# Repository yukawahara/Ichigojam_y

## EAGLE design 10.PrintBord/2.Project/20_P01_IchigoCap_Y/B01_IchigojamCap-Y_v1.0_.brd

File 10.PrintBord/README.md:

# フォルダ説明
* 0.Library
** パーツライブラリー、自作パーツ等を保存する

* 1.Tools
** Eagleで利用ツールを保存

* 2.Project
** Eagle でプロジェクトを作成した時に保存するもの
【プロジェクト命名規則】
プロジェクト名は下記とすること
```
年２桁_P連番_基盤名

例)
20_P01_EEPROM
```

【ボード命名規則】
プロジェクト名は下記とすること
```
B連番_基盤名_バージョン_備考

例)
B01_EEPROM_v1.0_〇〇
```

* 3.Order_Duplication
** 発注前に複製したデータを保存する。
** 保存する時は、「フォルダー」と「説明テキスト」を記載すること
【フォルダの命名規則】
```
年２桁_D連番_Pから始まるベースとなった基盤の番号-そのバージョン

例)
20_D01_P001-v1.0+P002-v1.0

```

* 10.Order
** 発注時に作成したデータを保存する。
** ここに保存するのは、ZIPファイルのみ
** 発注時に変更した時は

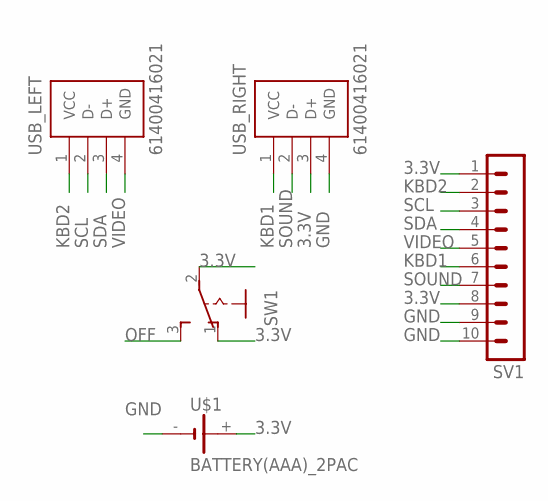
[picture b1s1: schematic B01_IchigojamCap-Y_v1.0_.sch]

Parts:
SV1: MA10-1
SW1: 255SB
U$1: BATTERY(AAA)_2PAC; BATTERY_HOLDER
USB_LEFT: 61400416021
USB_RIGHT: 61400416021

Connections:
3.3V: SV1.1, SV1.8, SW1.1 (O), SW1.2, U$1.+, USB_RIGHT.3 (D+)
GND: SV1.9, SV1.10, U$1.-, USB_RIGHT.4 (GND)
KBD1: SV1.6, USB_RIGHT.1 (VCC)
KBD2: SV1.2, USB_LEFT.1 (VCC)
OFF: SW1.3 (S)
SCL: SV1.3, USB_LEFT.2 (D-)
SDA: SV1.4, USB_LEFT.3 (D+)
SOUND: SV1.7, USB_RIGHT.2 (D-)
VIDEO: SV1.5, USB_LEFT.4 (GND)

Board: 2 copper layers, 5 parts (0 on the bottom side), 8 nets, no tracks yet.

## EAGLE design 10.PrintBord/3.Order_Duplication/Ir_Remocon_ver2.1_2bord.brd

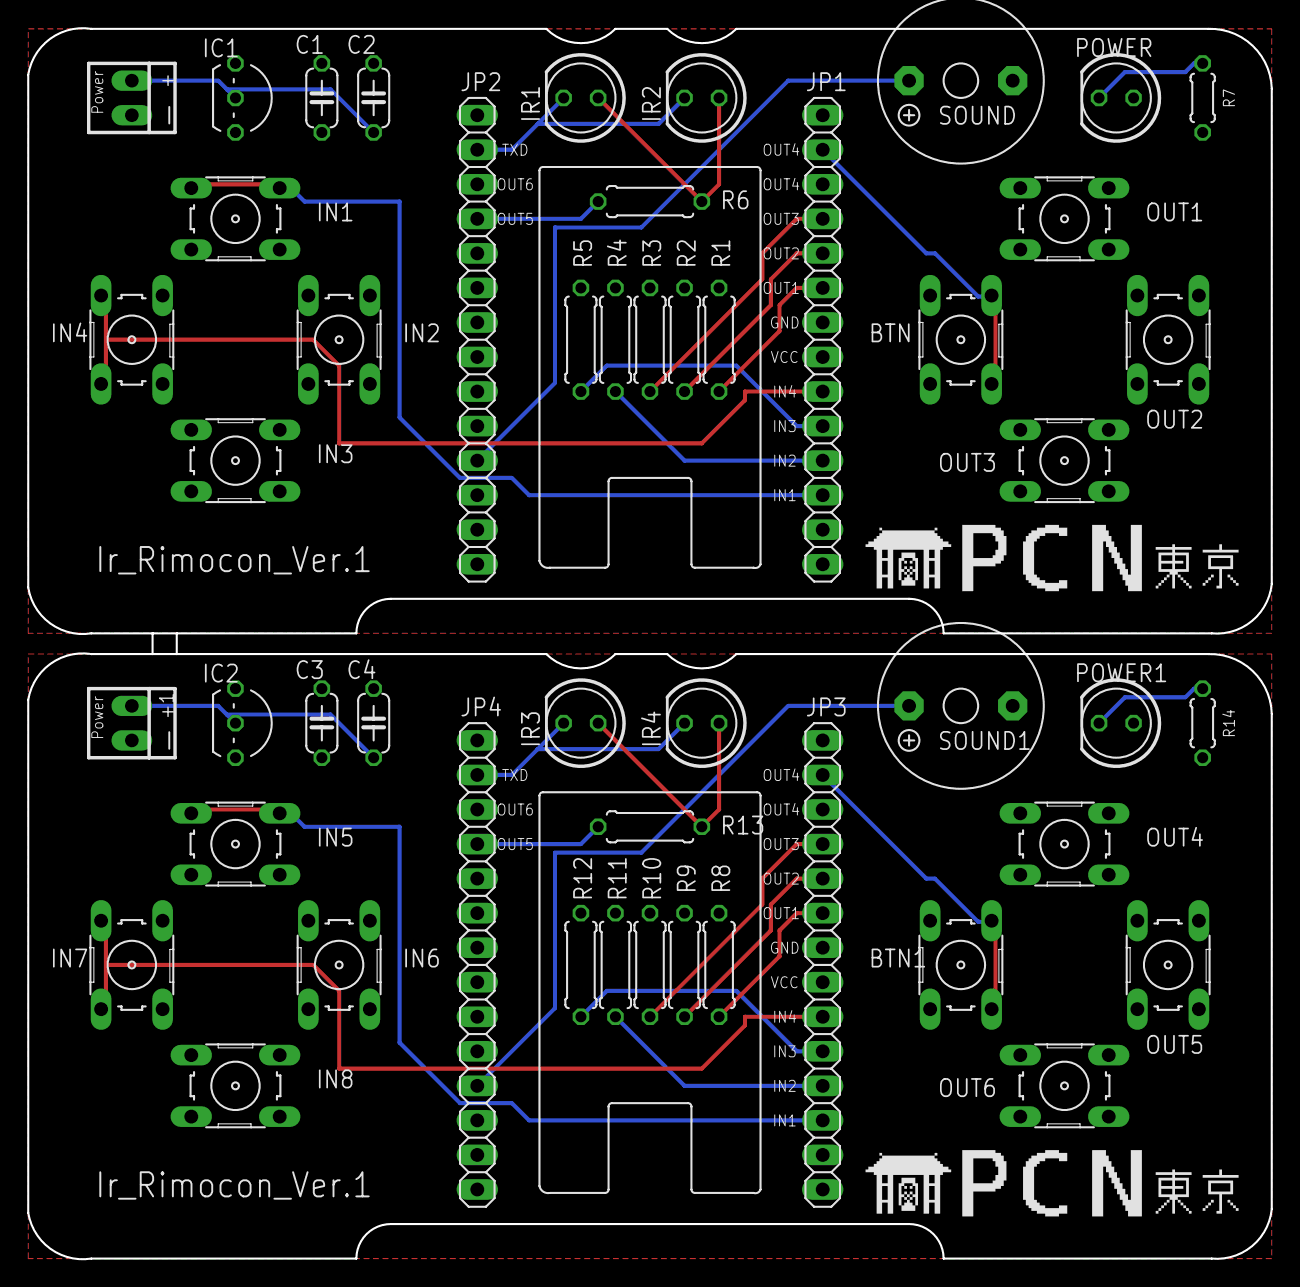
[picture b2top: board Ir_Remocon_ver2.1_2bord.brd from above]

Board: 2 copper layers, 91.4 x 90.5 mm, 50 parts (0 on the bottom side), 32 nets.

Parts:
+, +1: 22-23-2021
BTN, BTN1: B3F-10XX
C1, C2, C3, C4: C050-024X044
IC1, IC2: TO92-
IN1, IN2, IN3, IN4, IN5, IN6, IN7, IN8: B3F-10XX
IR1, IR2, IR3, IR4: LED5MM
JP1, JP2, JP3, JP4: 1X14
OUT1, OUT2, OUT3, OUT4, OUT5, OUT6: B3F-10XX
POWER, POWER1: LED5MM
R1, R2, R3, R4, R5, R8, R9, R10, R11, R12: 1KΩ; 0207/7
R6, R13: 100Ω; 0207/7
R7, R14: 330Ω; 0204/5
SOUND, SOUND1: F/TMB

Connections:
3.3V: C1.1, IC1.VOUT, IN2.1, IN2.2, IN3.1, IN3.2, JP1.8, JP2.7, OUT1.3, OUT1.4, OUT2.3, OUT2.4, OUT3.3, OUT3.4, POWER.A, R1.2, R2.2, R3.2, R4.1, R5.1
3.3V1: C3.1, IC2.VOUT, IN6.1, IN6.2, IN8.1, IN8.2, JP3.8, JP4.7, OUT4.3, OUT4.4, OUT5.3, OUT5.4, OUT6.3, OUT6.4, POWER1.A, R8.2, R9.2, R10.2, R11.1, R12.1
5V: +.1, C2.1, IC1.VIN
5V1: +1.1, C4.1, IC2.VIN
BTN: BTN.3, BTN.4, JP1.2
BTN1: BTN1.3, BTN1.4, JP3.2
GND: +.2, BTN.1, BTN.2, C1.2, C2.2, IC1.GND, IN1.3, IN1.4, IN2.3, IN2.4, IN3.3, IN3.4, IN4.3, IN4.4, JP1.7, JP2.8, OUT1.1, OUT1.2, OUT2.1, OUT2.2, OUT3.1, OUT3.2, R7.1, SOUND.-
GND1: +1.2, BTN1.1, BTN1.2, C3.2, C4.2, IC2.GND, IN5.3, IN5.4, IN6.3, IN6.4, IN7.3, IN7.4, IN8.3, IN8.4, JP3.7, JP4.8, OUT4.1, OUT4.2, OUT5.1, OUT5.2, OUT6.1, OUT6.2, R14.1, SOUND1.-
IN1: IN1.1, IN1.2, JP1.12
IN2: JP1.11, R4.2
IN3: JP1.10, R5.2
IN4: IN4.1, IN4.2, JP1.9
IN5: IN7.1, IN7.2, JP3.9
IN6: JP3.10, R12.2
IN7: JP3.11, R11.2
IN8: IN5.1, IN5.2, JP3.12
unnamed: IR1.A, IR2.A, R6.2
unnamed: POWER.K, R7.2
unnamed: IR3.A, IR4.A, R13.2
unnamed: POWER1.K, R14.2
OUT1: JP1.6, R1.1
OUT2: JP1.5, R2.1
OUT3: JP1.4, R3.1
OUT5: JP2.4, R6.1
OUT6: JP4.4, R13.1
OUT8: JP3.4, R10.1
OUT9: JP3.5, R9.1
OUT10: JP3.6, R8.1
SOUND: JP2.11, SOUND.+
SOUND1: JP4.11, SOUND1.+
TXD: IR1.K, IR2.K, JP2.2
TXD1: IR3.K, IR4.K, JP4.2

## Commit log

2020-02-23 Eagle7x Liblary commit
2020-02-24 LWeb_ibrary追加 IchigoCap基盤作成
2020-03-10 20200311

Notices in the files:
parts and their libraries:
USB_Wuerth_Elektronik_eiCan_Communicatio: Copyright: Würth Elektronik
